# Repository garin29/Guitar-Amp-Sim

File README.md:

# Guitar-Amp-Sim
Guitar Amp Sim

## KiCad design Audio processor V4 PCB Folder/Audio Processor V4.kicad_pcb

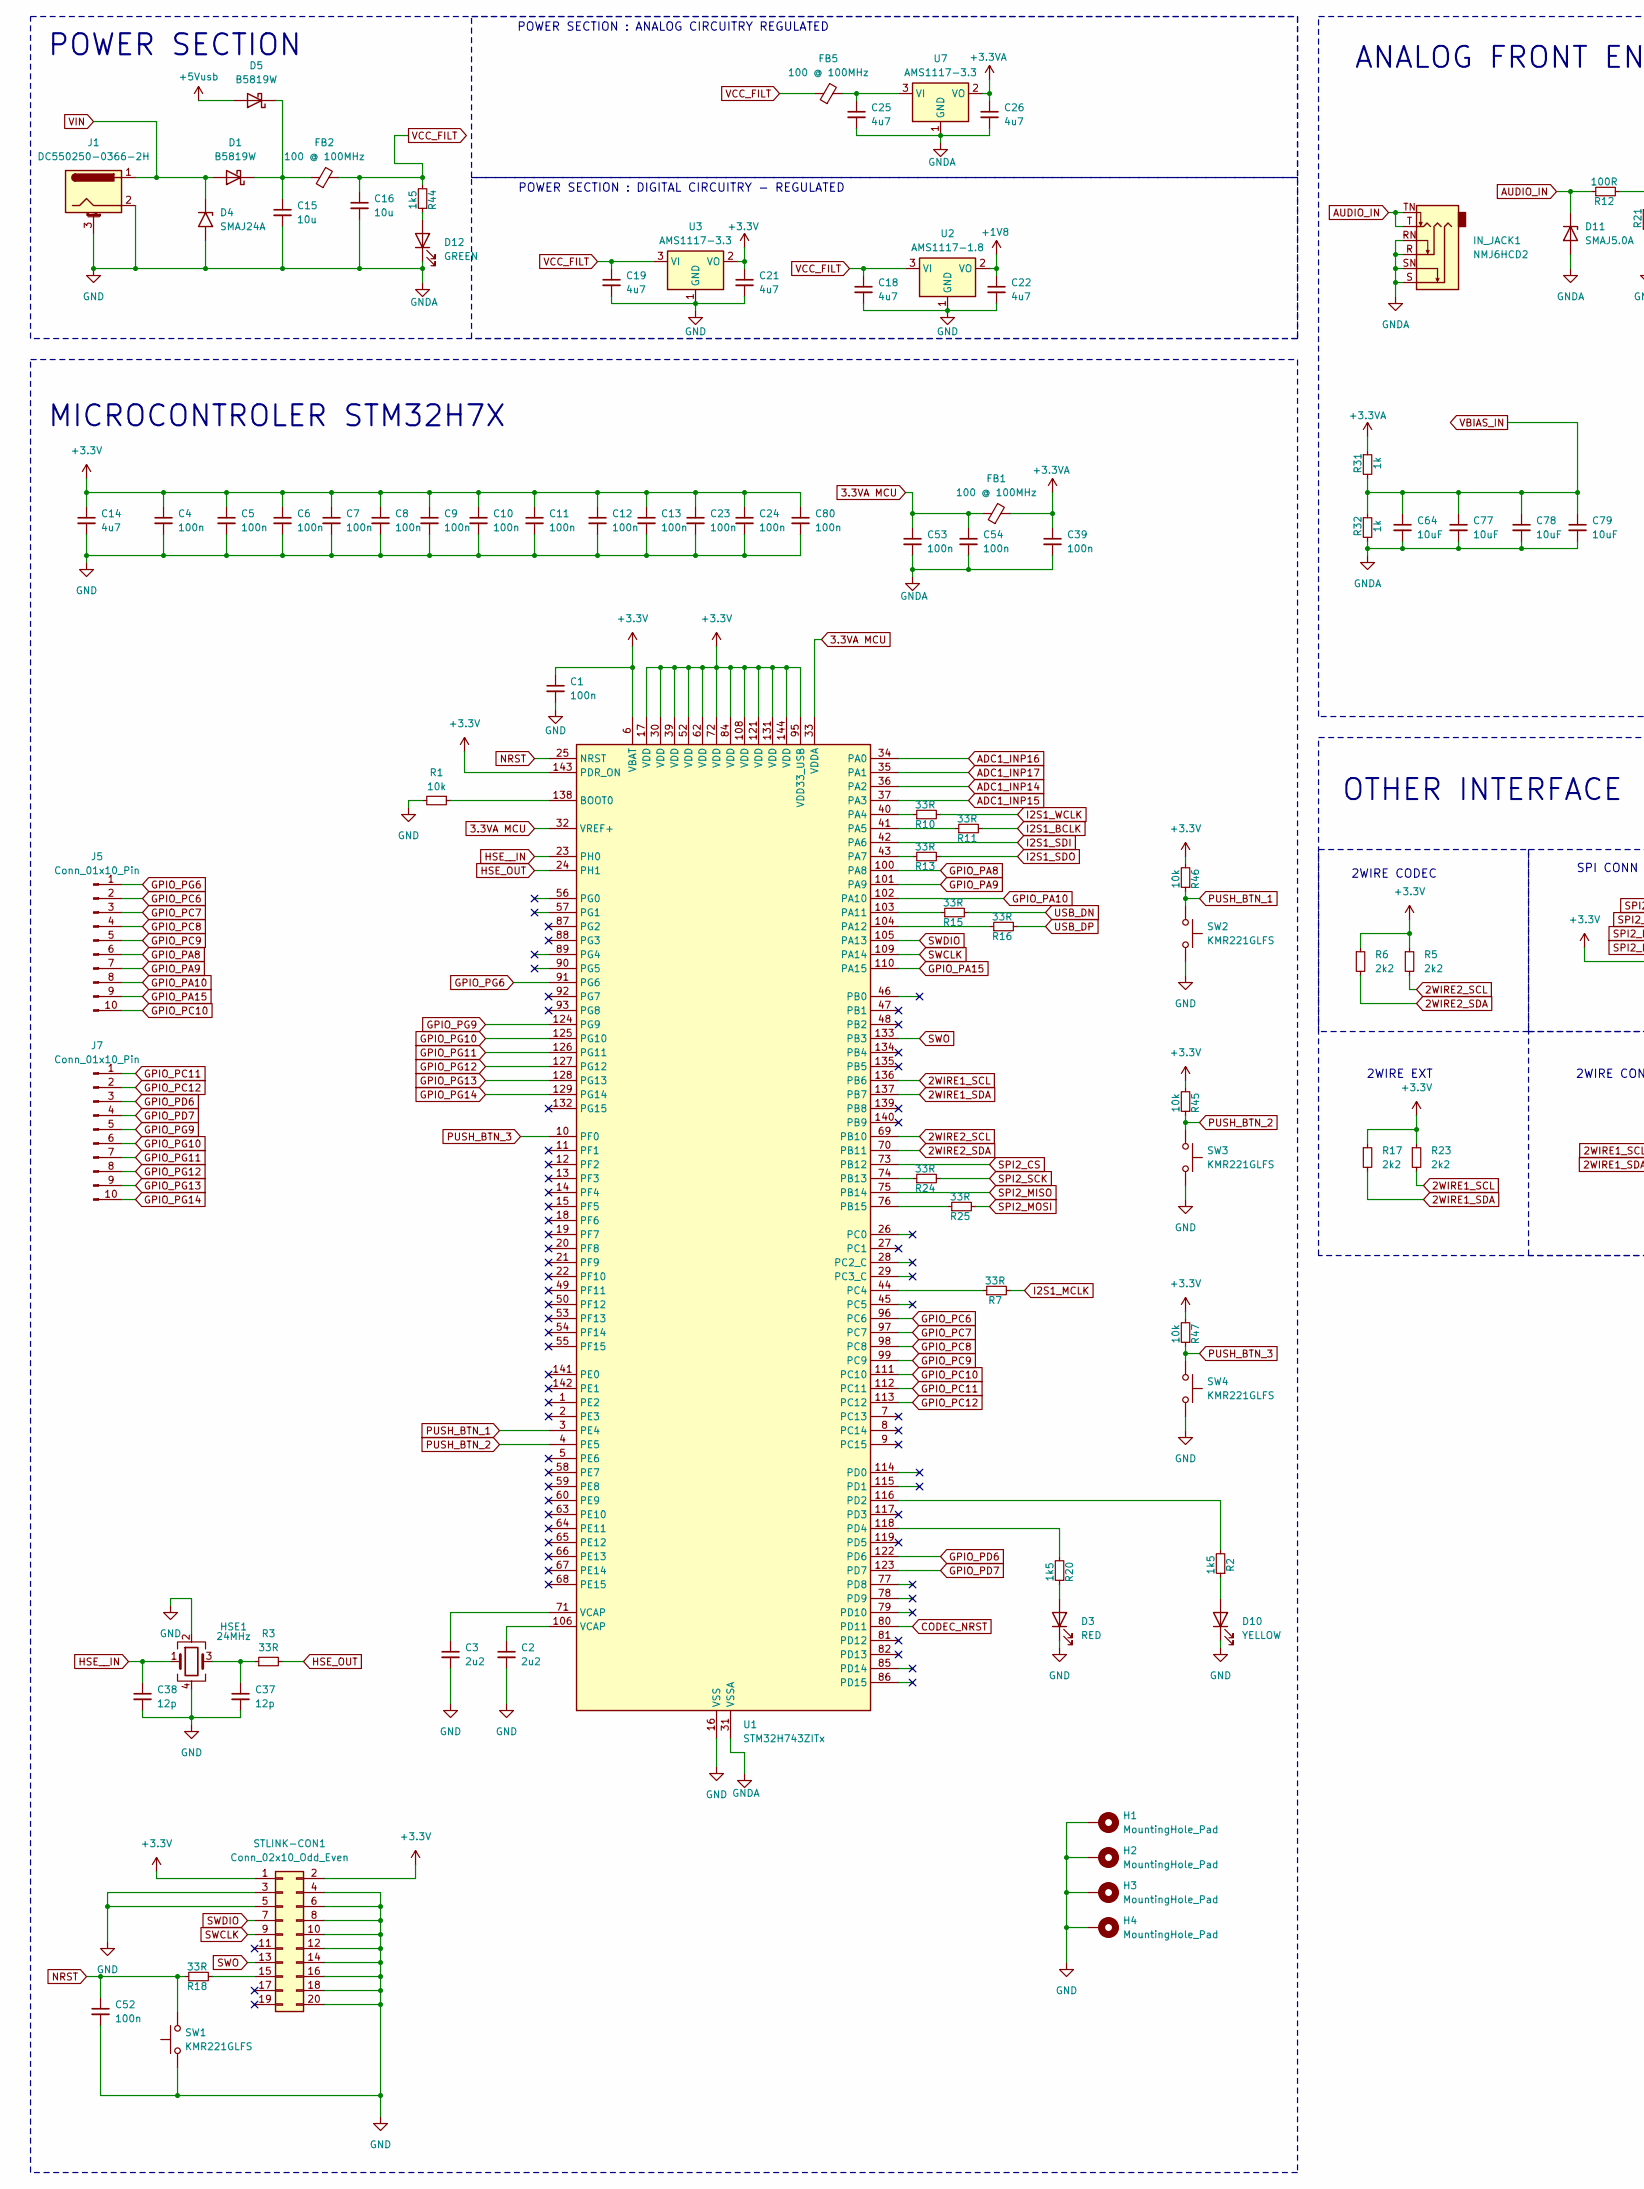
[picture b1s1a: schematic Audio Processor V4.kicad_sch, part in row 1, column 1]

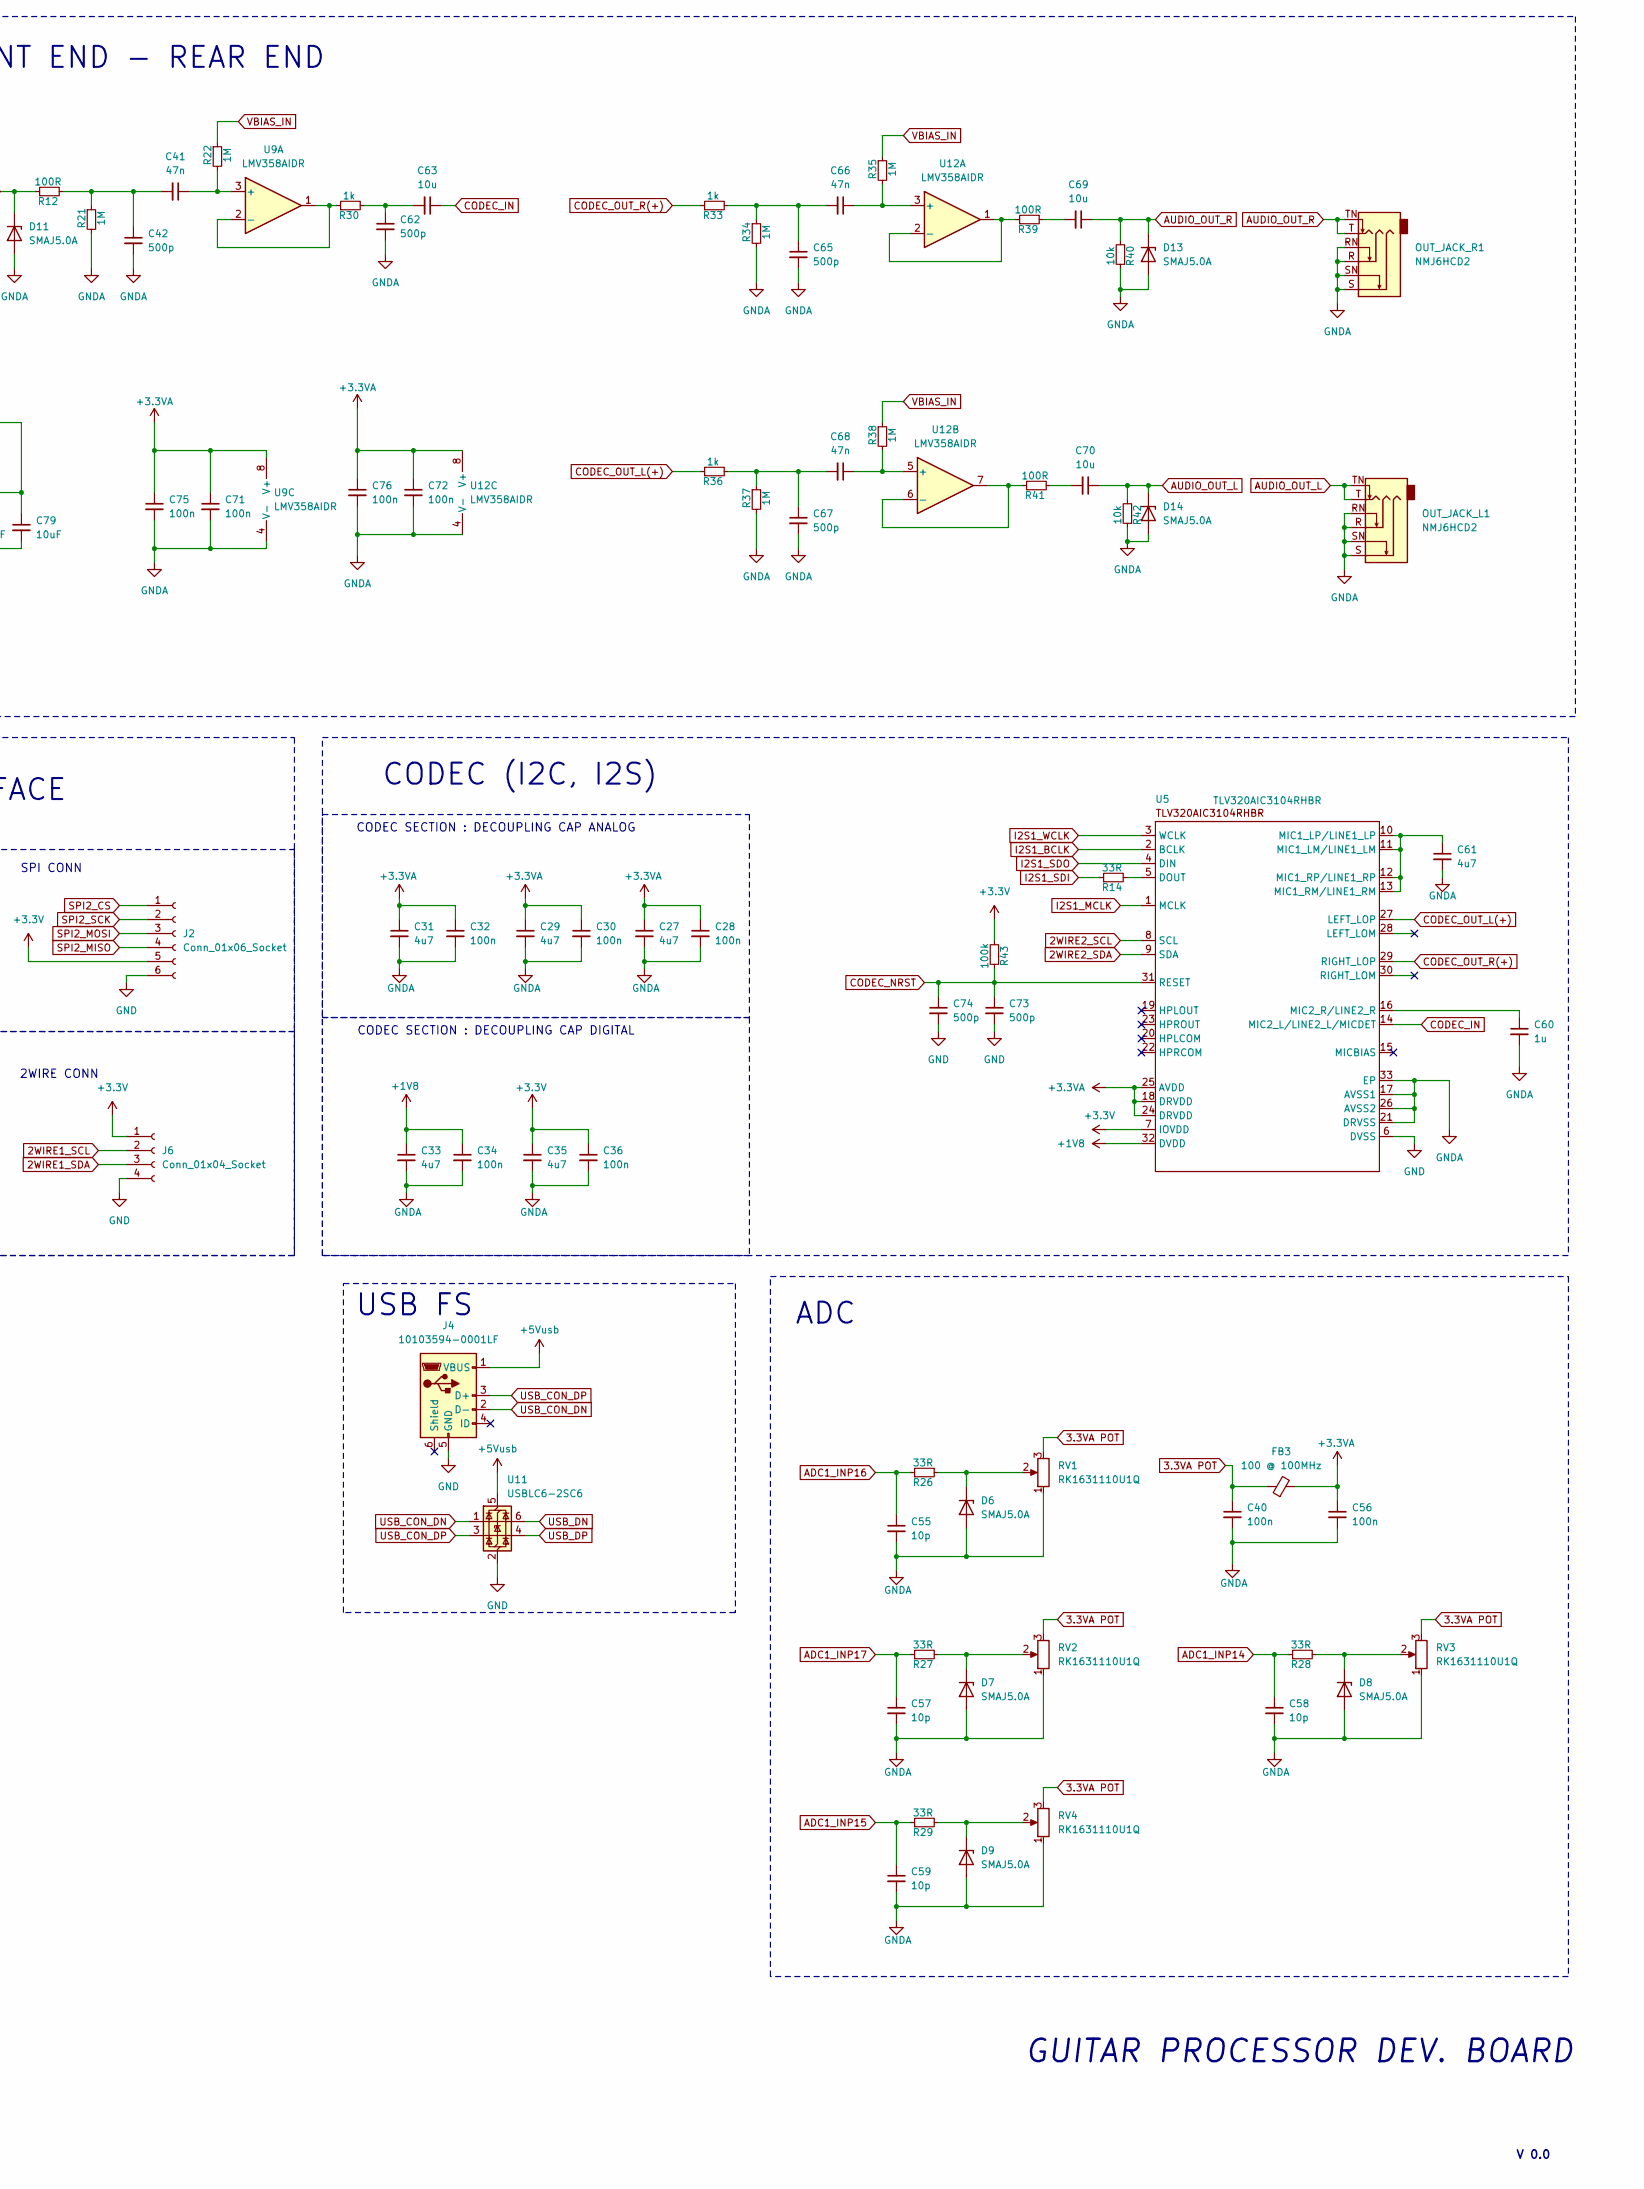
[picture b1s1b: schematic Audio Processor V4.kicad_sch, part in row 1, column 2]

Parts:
C1, C4, C5, C6, C7, C8, C9, C10, C11, C12, C13, C23, C24, C28, C30, C32, C34, C36, C39, C40, C52, C53, C54, C56, C71, C72, C75, C76, C80: 100n; C_0402_1005Metric; LCSC C1525
C2, C3: 2u2; C_0603_1608Metric; LCSC C1607
C14: 4u7; C_0603_1608Metric; LCSC C1705
C15, C16: 10u; C_1206_3216Metric; LCSC C1849
C18, C19, C21, C22, C25, C26, C27, C29, C31, C33, C35, C61: 4u7; C_0805_2012Metric; LCSC C1746
C37, C38: 12p; C_0402_1005Metric; LCSC C1547
C41, C66, C68: 47n; C_0603_1608Metric; LCSC C1622
C42: 500p; C_0603_1608Metric; LCSC C1747
C55, C57, C58, C59: 10p; C_0603_1608Metric; LCSC C1634
C60: 1u; C_0603_1608Metric; LCSC C1592
C62, C65, C67, C73, C74: 500p; C_0805_2012Metric; LCSC C1747
C63, C69, C70: 10u; C_0805_2012Metric; LCSC C1713
C64, C77, C78, C79: 10uF; C_0805_2012Metric; LCSC C1713
D1, D5: B5819W; D_SOD-123; LCSC C64885
D3: RED; LED_0603_1608Metric; LCSC C2286
D4: SMAJ24A; D_SMA; LCSC C148222
D6, D7, D8, D9, D11, D13, D14: SMAJ5.0A; D_SMA; LCSC C113952
D10: YELLOW; LED_0603_1608Metric; LCSC C2287
D12: GREEN; LED_0805_2012Metric; LCSC C2297
FB1, FB2, FB3, FB5: 100 @ 100MHz; L_0805_2012Metric; LCSC C1015
H1, H2, H3, H4: MountingHole_Pad; MountingHole_4.3mm_M4_Pad_Via
HSE1: 24MHz; Crystal_SMD_3225-4Pin_3.2x2.5mm; LCSC C15643
IN_JACK1: NMJ6HCD2; Jack_6.35mm_Neutrik_NMJ6HCD2_Horizontal; LCSC C368502
J1: DC550250-0366-2H; BarrelJack_Horizontal; LCSC C7428747
J2: Conn_01x06_Socket; PinSocket_1x06_P2.54mm_Vertical; LCSC C40877
J4: 10103594-0001LF; USB_Micro-B_Amphenol_10103594-0001LF_Horizontal; LCSC C428495
J5, J7: Conn_01x10_Pin; PinSocket_1x10_P2.54mm_Vertical; LCSC C22438160
J6: Conn_01x04_Socket; PinSocket_1x04_P2.54mm_Vertical; LCSC C2718488
OUT_JACK_L1: NMJ6HCD2; Jack_6.35mm_Neutrik_NMJ6HCD2_Horizontal; LCSC C368502
OUT_JACK_R1: NMJ6HCD2; Jack_6.35mm_Neutrik_NMJ6HCD2_Horizontal; LCSC C368502
R1, R40, R42, R45, R46, R47: 10k; R_0402_1005Metric; LCSC C25744
R2, R20, R44: 1k5; R_0603_1608Metric; LCSC C22843
R3, R7, R10, R11, R13, R14, R15, R16, R18, R24, R25, R26, R27, R28, R29: 33R; R_0402_1005Metric; LCSC C25105
R5, R6, R17, R23: 2k2; R_0603_1608Metric; LCSC C4190
R12, R39, R41: 100R; R_0402_1005Metric; LCSC C25076
R21, R22, R34, R35, R37, R38: 1M; R_0402_1005Metric; LCSC C26083
R30, R31, R32, R33, R36: 1k; R_0402_1005Metric; LCSC C11702
R43: 100k; C_0402_1005Metric; LCSC C25530
RV1, RV2, RV3, RV4: RK1631110U1Q; Potentiometer_Alps_RK163_Single_Horizontal; LCSC C370978
STLINK-CON1: Conn_02x10_Odd_Even; PinHeader_2x10_P2.54mm_Vertical; LCSC C3405
SW1, SW2, SW3, SW4: KMR221GLFS; SW_Push_1P1T_NO_CK_KMR2; LCSC C72443
U1: STM32H743ZITx; LQFP-144_20x20mm_P0.5mm; LCSC C114408
U2: AMS1117-1.8; SOT-223-3_TabPin2; LCSC C6185
U3, U7: AMS1117-3.3; SOT-223-3_TabPin2; LCSC C6186
U5: TLV320AIC3104RHBR; VQFN-32-1EP_5x5mm_P0.5mm_EP3.5x3.5mm_ThermalVias; LCSC C181753
U9, U12: LMV358AIDR; PowerIntegrations_SO-8; LCSC C182039
U11: USBLC6-2SC6; TSOT-23-6; LCSC C2687116

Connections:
2WIRE1_SCL: J6.2, R23.2, U1.136 (PB6)
2WIRE1_SDA: J6.3, R17.2, U1.137 (PB7)
2WIRE2_SCL: R5.2, U1.69 (PB10), U5.8 (SCL)
2WIRE2_SDA: R6.2, U1.70 (PB11), U5.9 (SDA)
3.3VA MCU: C53.1, C54.1, FB1.1, U1.32 (VREF+), U1.33 (VDDA)
3.3VA POT: C40.1, FB3.1, RV1.3, RV2.3, RV3.3, RV4.3
+1V8: C22.1, C33.1, C34.1, U2.2 (VO), U5.32 (DVDD)
+3.3V: C1.1, C4.1, C5.1, C6.1, C7.1, C8.1, C9.1, C10.1, C11.1, C12.1, C13.1, C14.1, C21.1, C23.1, C24.1, C35.1, C36.1, C80.1, J2.5, J6.1, R5.1, R6.1, R17.1, R23.1, R43.2, R45.2, R46.2, R47.2, STLINK-CON1.1, STLINK-CON1.2, U1.6 (VBAT), U1.17 (VDD), U1.30 (VDD), U1.39 (VDD), U1.52 (VDD), U1.62 (VDD), U1.72 (VDD), U1.84 (VDD), U1.95 (VDD33_USB), U1.108 (VDD), U1.121 (VDD), U1.131 (VDD), U1.143 (PDR_ON), U1.144 (VDD), U3.2 (VO), U5.7 (IOVDD)
+3.3VA: C26.1, C27.1, C28.1, C29.1, C30.1, C31.1, C32.1, C39.1, C56.1, C71.1, C72.1, C75.1, C76.1, FB1.2, FB3.2, R31.1, U5.18 (DRVDD), U5.24 (DRVDD), U5.25 (AVDD), U7.2 (VO), U9.8 (V+), U12.8 (V+)
+5Vusb: D5.2 (A), J4.1 (VBUS), U11.5 (VBUS)
ADC1_INP14: C58.1, R28.1, U1.36 (PA2)
ADC1_INP15: C59.1, R29.1, U1.37 (PA3)
ADC1_INP16: C55.1, R26.1, U1.34 (PA0)
ADC1_INP17: C57.1, R27.1, U1.35 (PA1)
AUDIO_IN: D11.1 (K), IN_JACK1.T, IN_JACK1.TN, R12.1
AUDIO_OUT_L: C70.1, D14.1 (K), OUT_JACK_L1.T, OUT_JACK_L1.TN, R42.2
AUDIO_OUT_R: C69.1, D13.1 (K), OUT_JACK_R1.T, OUT_JACK_R1.TN, R40.2
CODEC_IN: C63.1, U5.14 (MIC2_L/LINE2_L/MICDET)
CODEC_NRST: C73.1, C74.1, R43.1, U1.80 (PD11), U5.31 (RESET)
CODEC_OUT_L(+): R36.1, U5.27 (LEFT_LOP)
CODEC_OUT_R(+): R33.1, U5.29 (RIGHT_LOP)
GND: C1.2, C2.2, C3.2, C4.2, C5.2, C6.2, C7.2, C8.2, C9.2, C10.2, C11.2, C12.2, C13.2, C14.2, C15.2, C16.2, C18.2, C19.2, C21.2, C22.2, C23.2, C24.2, C25.2, C26.2, C27.2, C28.2, C29.2, C30.2, C31.2, C32.2, C33.2, C34.2, C35.2, C36.2, C37.2, C38.2, C39.2, C40.2, C42.2, C52.2, C53.2, C54.2, C55.2, C56.2, C57.2, C58.2, C59.2, C60.2, C61.2, C62.2, C64.2, C65.2, C67.2, C71.2, C72.2, C73.2, C74.2, C75.2, C76.2, C77.2, C78.2, C79.2, C80.2, D3.1 (K), D4.2 (A2), D6.2 (A), D7.2 (A), D8.2 (A), D9.2 (A), D10.1 (K), D11.2 (A), D12.1 (K), D13.2 (A), D14.2 (A), H1.1, H2.1, H3.1, H4.1, HSE1.2, HSE1.4, IN_JACK1.R, IN_JACK1.RN, IN_JACK1.S, IN_JACK1.SN, J1.2, J1.3 (MountPin), J2.6, J4.5 (GND), J6.4, OUT_JACK_L1.R, OUT_JACK_L1.RN, OUT_JACK_L1.S, OUT_JACK_L1.SN, OUT_JACK_R1.R, OUT_JACK_R1.RN, OUT_JACK_R1.S, OUT_JACK_R1.SN, R1.2, R21.2, R32.2, R34.2, R37.2, R40.1, R42.1, RV1.1, RV2.1, RV3.1, RV4.1, STLINK-CON1.3, STLINK-CON1.4, STLINK-CON1.5, STLINK-CON1.6, STLINK-CON1.8, STLINK-CON1.10, STLINK-CON1.12, STLINK-CON1.14, STLINK-CON1.16, STLINK-CON1.18, STLINK-CON1.20, SW1.1, SW2.2, SW3.2, SW4.2, U1.16 (VSS), U1.31 (VSSA), U1.38 (VSS), U1.51 (VSS), U1.61 (VSS), U1.83 (VSS), U1.94 (VSS), U1.107 (VSS), U1.120 (VSS), U1.130 (VSS), U2.1 (GND), U3.1 (GND), U5.6 (DVSS), U5.17 (AVSS1), U5.21 (DRVSS), U5.26 (AVSS2), U5.33 (EP), U7.1 (GND), U9.4 (V-), U11.2 (GND), U12.4 (V-)
GPIO_PA8: J5.6, U1.100 (PA8)
GPIO_PA9: J5.7, U1.101 (PA9)
GPIO_PA10: J5.8, U1.102 (PA10)
GPIO_PA15: J5.9, U1.110 (PA15)
GPIO_PC6: J5.2, U1.96 (PC6)
GPIO_PC7: J5.3, U1.97 (PC7)
GPIO_PC8: J5.4, U1.98 (PC8)
GPIO_PC9: J5.5, U1.99 (PC9)
GPIO_PC10: J5.10, U1.111 (PC10)
GPIO_PC11: J7.1, U1.112 (PC11)
GPIO_PC12: J7.2, U1.113 (PC12)
GPIO_PD6: J7.3, U1.122 (PD6)
GPIO_PD7: J7.4, U1.123 (PD7)
GPIO_PG6: J5.1, U1.91 (PG6)
GPIO_PG9: J7.5, U1.124 (PG9)
GPIO_PG10: J7.6, U1.125 (PG10)
GPIO_PG11: J7.7, U1.126 (PG11)
GPIO_PG12: J7.8, U1.127 (PG12)
GPIO_PG13: J7.9, U1.128 (PG13)
GPIO_PG14: J7.10, U1.129 (PG14)
HSE_OUT: R3.2, U1.24 (PH1)
HSE__IN: C38.1, HSE1.1, U1.23 (PH0)
I2S1_BCLK: R11.2, U5.2 (BCLK)
I2S1_MCLK: R7.2, U5.1 (MCLK)
I2S1_SDI: R14.1, U1.42 (PA6)
I2S1_SDO: R13.2, U5.4 (DIN)
I2S1_WCLK: R10.2, U5.3 (WCLK)
NRST: C52.1, R18.1, SW1.2, U1.25 (NRST)
unnamed: C2.1, U1.106 (VCAP)
unnamed: C3.1, U1.71 (VCAP)
unnamed: C37.1, HSE1.3, R3.1
unnamed: C41.2, C42.1, R12.2, R21.1
unnamed: C62.1, C63.2, R30.2
unnamed: C65.1, C66.2, R33.2, R34.1
unnamed: C67.1, C68.2, R36.2, R37.1
unnamed: C69.2, R39.2
unnamed: C70.2, R41.2
unnamed: C15.1, D1.1 (K), D5.1 (K), FB2.1
unnamed: D3.2 (A), R20.1
unnamed: D6.1 (K), R26.2, RV1.2
unnamed: D7.1 (K), R27.2, RV2.2
unnamed: D8.1 (K), R28.2, RV3.2
unnamed: D9.1 (K), R29.2, RV4.2
unnamed: D10.2 (A), R2.1
unnamed: D12.2 (A), R44.1
unnamed: R18.2, STLINK-CON1.15
unnamed: R1.1, U1.138 (BOOT0)
unnamed: R10.1, U1.40 (PA4)
unnamed: R11.1, U1.41 (PA5)
unnamed: R13.1, U1.43 (PA7)
unnamed: R15.1, U1.103 (PA11)
unnamed: R16.1, U1.104 (PA12)
unnamed: R24.1, U1.74 (PB13)
unnamed: R25.1, U1.76 (PB15)
unnamed: R7.1, U1.44 (PC4)
unnamed: R2.2, U1.116 (PD2)
unnamed: R20.2, U1.118 (PD4)
unnamed: R14.2, U5.5 (DOUT)
unnamed: C61.1, U5.10 (MIC1_LP/LINE1_LP), U5.11 (MIC1_LM/LINE1_LM), U5.12 (MIC1_RP/LINE1_RP), U5.13 (MIC1_RM/LINE1_RM)
unnamed: C60.1, U5.16 (MIC2_R/LINE2_R)
unnamed: C25.1, FB5.2, U7.3 (VI)
unnamed: C41.1, R22.2, U9.3 (+)
unnamed: R30.1, U9.1, U9.2 (-)
unnamed: C66.1, R35.2, U12.3 (+)
unnamed: R39.1, U12.1, U12.2 (-)
unnamed: C68.1, R38.2, U12.5 (+)
unnamed: R41.1, U12.6 (-), U12.7
PUSH_BTN_1: R46.1, SW2.1, U1.3 (PE4)
PUSH_BTN_2: R45.1, SW3.1, U1.4 (PE5)
PUSH_BTN_3: R47.1, SW4.1, U1.10 (PF0)
SPI2_CS: J2.1, U1.73 (PB12)
SPI2_MISO: J2.4, U1.75 (PB14)
SPI2_MOSI: J2.3, R25.2
SPI2_SCK: J2.2, R24.2
SWCLK: STLINK-CON1.9, U1.109 (PA14)
SWDIO: STLINK-CON1.7, U1.105 (PA13)
SWO: STLINK-CON1.13, U1.133 (PB3)
USB_CON_DN: J4.2 (D-), U11.1 (I/O1)
USB_CON_DP: J4.3 (D+), U11.3 (I/O2)
USB_DN: R15.2, U11.6 (I/O1)
USB_DP: R16.2, U11.4 (I/O2)
VBIAS_IN: C64.1, C77.1, C78.1, C79.1, R22.1, R31.2, R32.1, R35.1, R38.1
VCC_FILT: C16.1, C18.1, C19.1, FB2.2, FB5.1, R44.2, U2.3 (VI), U3.3 (VI)
VIN: D1.2 (A), D4.1 (A1), J1.1

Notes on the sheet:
MICROCONTROLER STM32H7X
OTHER INTERFACE
POWER SECTION : DIGITAL CIRCUITRY - REGULATED
CODEC SECTION : DECOUPLING CAP DIGITAL
POWER SECTION : ANALOG CIRCUITRY REGULATED
GUITAR PROCESSOR DEV. BOARD
2WIRE CODEC
USB FS
POWER SECTION
SPI CONN
CODEC SECTION : DECOUPLING CAP ANALOG
ANALOG FRONT END - REAR END
CODEC (I2C, I2S)
V 0.0
2WIRE EXT
ADC
2WIRE CONN

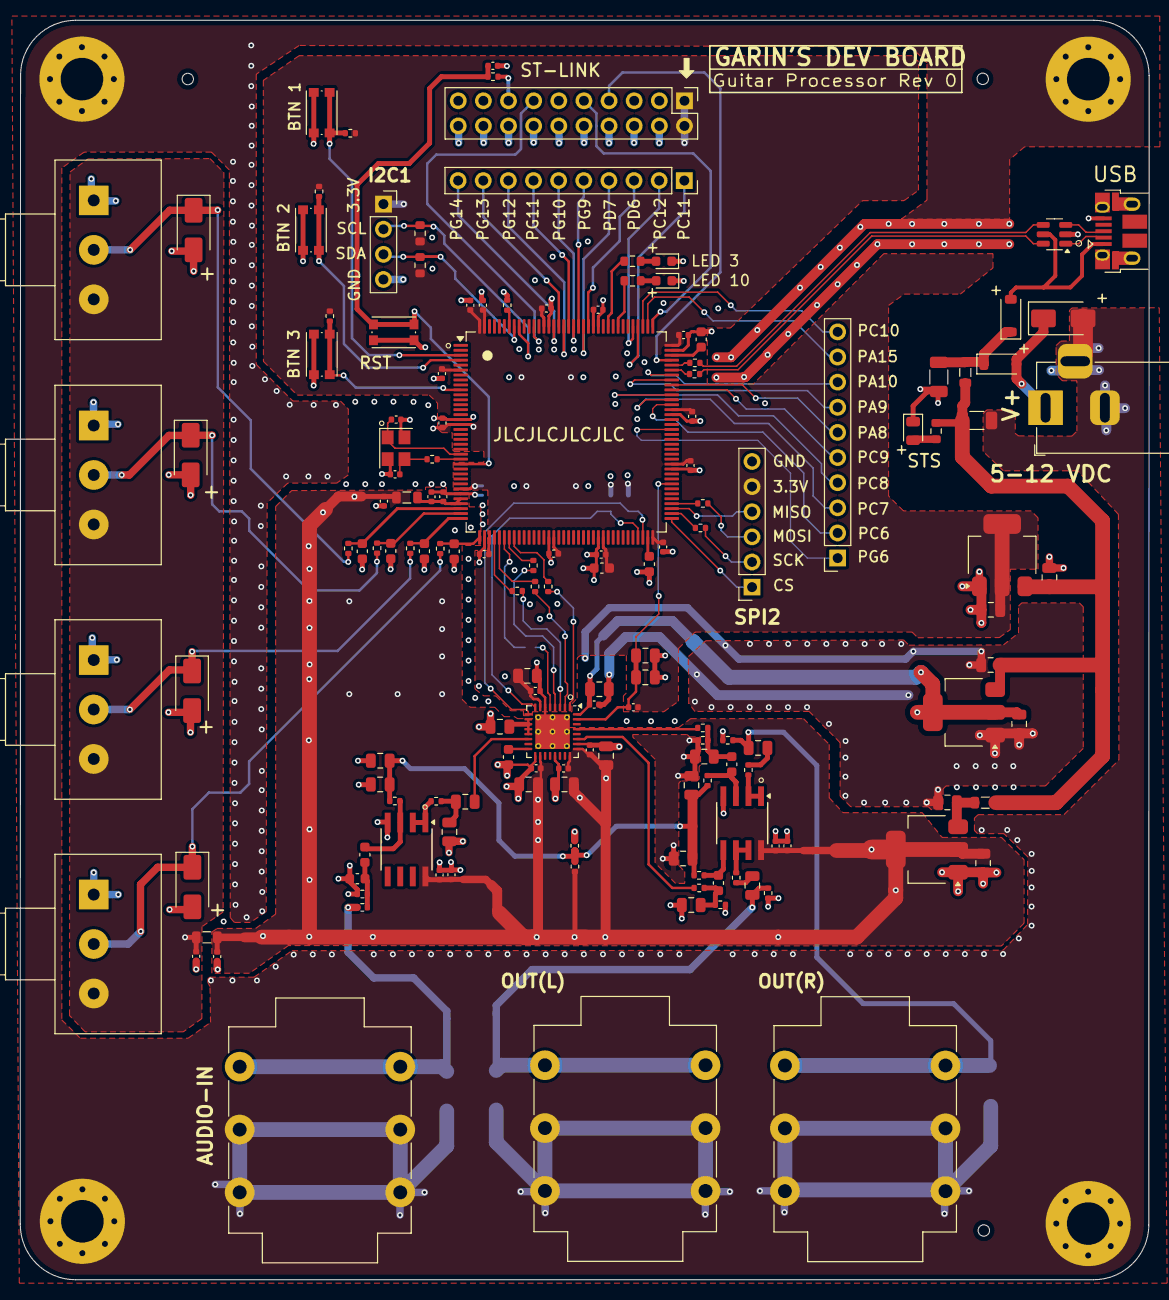
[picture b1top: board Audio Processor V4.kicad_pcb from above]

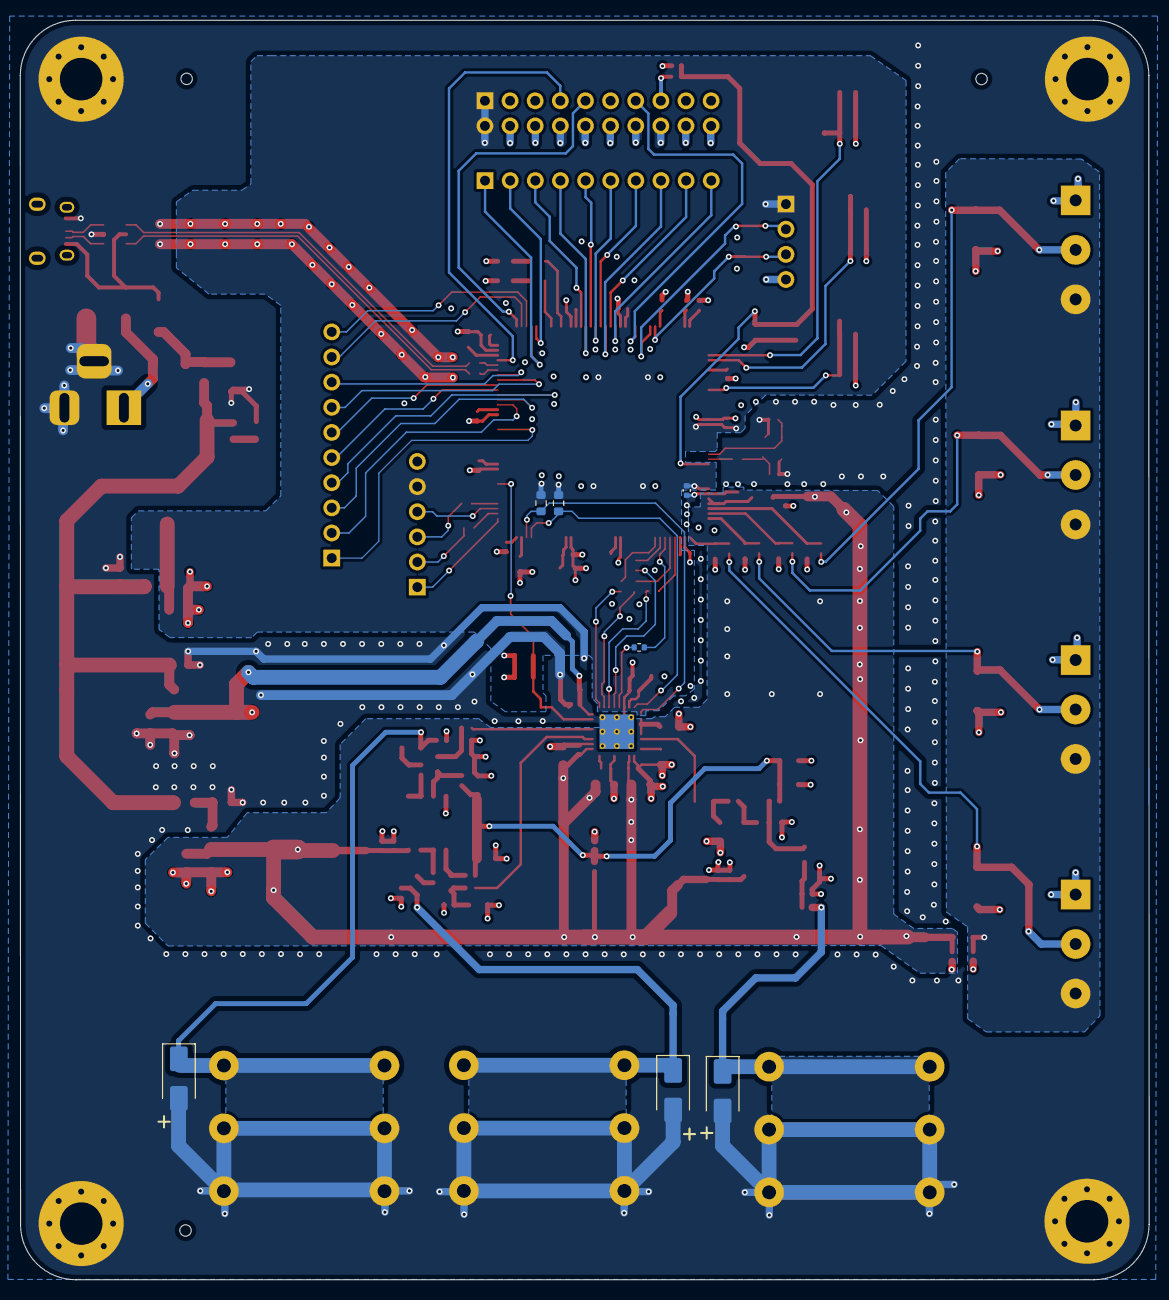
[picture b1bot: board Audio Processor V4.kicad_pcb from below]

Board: 4 copper layers, 114.1 x 127.3 mm, 160 parts (7 on the bottom side), 106 nets.

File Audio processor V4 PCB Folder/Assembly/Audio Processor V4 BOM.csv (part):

"Comment","Designator","Footprint","LCSC"
"Conn_01x10_Pin","J7","Connector_PinSocket_2.54mm:PinSocket_1x10_P2.54mm_Vertical","C22438160"
"Conn_01x10_Pin","J5","Connector_PinSocket_2.54mm:PinSocket_1x10_P2.54mm_Vertical","C22438160"
"DC550250-0366-2H","J1","Connector_BarrelJack:BarrelJack_Horizontal","C7428747"
"Conn_01x04_Socket","J6","Connector_PinSocket_2.54mm:PinSocket_1x04_P2.54mm_Vertical","C2718488"
"USBLC6-2SC6","U11","Package_TO_SOT_SMD:TSOT-23-6","C2687116"
"10103594-0001LF","J4","Connector_USB:USB_Micro-B_Amphenol_10103594-0001LF_Horizontal","C428495"
"RK1631110U1Q","RV4","Potentiometer_THT:Potentiometer_Alps_RK163_Single_Horizontal","C370978"
"RK1631110U1Q","RV3","Potentiometer_THT:Potentiometer_Alps_RK163_Single_Horizontal","C370978"
"RK1631110U1Q","RV2","Potentiometer_THT:Potentiometer_Alps_RK163_Single_Horizontal","C370978"
"RK1631110U1Q","RV1","Potentiometer_THT:Potentiometer_Alps_RK163_Single_Horizontal","C370978"
"NMJ6HCD2","OUT_JACK_R1","Connector_Audio:Jack_6.35mm_Neutrik_NMJ6HCD2_Horizontal","C368502"
"NMJ6HCD2","OUT_JACK_L1","Connector_Audio:Jack_6.35mm_Neutrik_NMJ6HCD2_Horizontal","C368502"
"NMJ6HCD2","IN_JACK1","Connector_Audio:Jack_6.35mm_Neutrik_NMJ6HCD2_Horizontal","C368502"
"LMV358AIDR","U12","Package_SO:PowerIntegrations_SO-8","C182039"
"LMV358AIDR","U9","Package_SO:PowerIntegrations_SO-8","C182039"
"TLV320AIC3104RHBR","U5","Package_DFN_QFN:VQFN-32-1EP_5x5mm_P0.5mm_EP3.5x3.5mm_ThermalVias","C181753"
"SMAJ24A","D4","Diode_SMD:D_SMA","C148222"
"STM32H743ZITx","U1","Package_QFP:LQFP-144_20x20mm_P0.5mm","C114408"
"SMAJ5.0A","D14","Diode_SMD:D_SMA","C113952"
"SMAJ5.0A","D13","Diode_SMD:D_SMA","C113952"
"SMAJ5.0A","D11","Diode_SMD:D_SMA","C113952"
"SMAJ5.0A","D9","Diode_SMD:D_SMA","C113952"
"SMAJ5.0A","D8","Diode_SMD:D_SMA","C113952"
"SMAJ5.0A","D7","Diode_SMD:D_SMA","C113952"
"SMAJ5.0A","D6","Diode_SMD:D_SMA","C113952"
"KMR221GLFS","SW4","Button_Switch_SMD:SW_Push_1P1T_NO_CK_KMR2","C72443"
"KMR221GLFS","SW3","Button_Switch_SMD:SW_Push_1P1T_NO_CK_KMR2","C72443"
"KMR221GLFS","SW2","Button_Switch_SMD:SW_Push_1P1T_NO_CK_KMR2","C72443"
"KMR221GLFS","SW1","Button_Switch_SMD:SW_Push_1P1T_NO_CK_KMR2","C72443"
"B5819W","D5","Diode_SMD:D_SOD-123","C64885"
"B5819W","D1","Diode_SMD:D_SOD-123","C64885"
"Conn_01x06_Socket","J2","Connector_PinSocket_2.54mm:PinSocket_1x06_P2.54mm_Vertical","C40877"
"1M","R38","Resistor_SMD:R_0402_1005Metric","C26083"
"1M","R37","Resistor_SMD:R_0402_1005Metric","C26083"
"1M","R35","Resistor_SMD:R_0402_1005Metric","C26083"
"1M","R34","Resistor_SMD:R_0402_1005Metric","C26083"
"1M","R22","Resistor_SMD:R_0402_1005Metric","C26083"
"1M","R21","Resistor_SMD:R_0402_1005Metric","C26083"
"10k","R47","Resistor_SMD:R_0402_1005Metric","C25744"
"10k","R46","Resistor_SMD:R_0402_1005Metric","C25744"
"10k","R45","Resistor_SMD:R_0402_1005Metric","C25744"
"10k","R42","Resistor_SMD:R_0402_1005Metric","C25744"
"10k","R40","Resistor_SMD:R_0402_1005Metric","C25744"
"10k","R1","Resistor_SMD:R_0402_1005Metric","C25744"
"100k","R43","Capacitor_SMD:C_0402_1005Metric","C25530"
"33R","R29","Resistor_SMD:R_0402_1005Metric","C25105"
"33R","R28","Resistor_SMD:R_0402_1005Metric","C25105"
"33R","R27","Resistor_SMD:R_0402_1005Metric","C25105"
"33R","R26","Resistor_SMD:R_0402_1005Metric","C25105"
"33R","R25","Resistor_SMD:R_0402_1005Metric","C25105"
"33R","R24","Resistor_SMD:R_0402_1005Metric","C25105"
"33R","R18","Resistor_SMD:R_0402_1005Metric","C25105"
"33R","R16","Resistor_SMD:R_0402_1005Metric","C25105"
"33R","R15","Resistor_SMD:R_0402_1005Metric","C25105"
"33R","R14","Resistor_SMD:R_0402_1005Metric","C25105"
"33R","R13","Resistor_SMD:R_0402_1005Metric","C25105"
"33R","R11","Resistor_SMD:R_0402_1005Metric","C25105"
"33R","R10","Resistor_SMD:R_0402_1005Metric","C25105"
"33R","R7","Resistor_SMD:R_0402_1005Metric","C25105"
"33R","R3","Resistor_SMD:R_0402_1005Metric","C25105"
"100R","R41","Resistor_SMD:R_0402_1005Metric","C25076"
"100R","R39","Resistor_SMD:R_0402_1005Metric","C25076"
"100R","R12","Resistor_SMD:R_0402_1005Metric","C25076"
"1k5","R44","Resistor_SMD:R_0603_1608Metric","C22843"
"1k5","R20","Resistor_SMD:R_0603_1608Metric","C22843"
"1k5","R2","Resistor_SMD:R_0603_1608Metric","C22843"
"24MHz","HSE1","Crystal:Crystal_SMD_3225-4Pin_3.2x2.5mm","C15643"
"1k","R36","Resistor_SMD:R_0402_1005Metric","C11702"
"1k","R33","Resistor_SMD:R_0402_1005Metric","C11702"
"1k","R32","Resistor_SMD:R_0402_1005Metric","C11702"
"1k","R31","Resistor_SMD:R_0402_1005Metric","C11702"
"1k","R30","Resistor_SMD:R_0402_1005Metric","C11702"
"AMS1117-3.3","U7","Package_TO_SOT_SMD:SOT-223-3_TabPin2","C6186"
"AMS1117-3.3","U3","Package_TO_SOT_SMD:SOT-223-3_TabPin2","C6186"
"AMS1117-1.8","U2","Package_TO_SOT_SMD:SOT-223-3_TabPin2","C6185"
"2k2","R23","Resistor_SMD:R_0603_1608Metric","C4190"
"2k2","R17","Resistor_SMD:R_0603_1608Metric","C4190"
"2k2","R6","Resistor_SMD:R_0603_1608Metric","C4190"
"2k2","R5","Resistor_SMD:R_0603_1608Metric","C4190"
"Conn_02x10_Odd_Even","STLINK-CON1","Connector_PinHeader_2.54mm:PinHeader_2x10_P2.54mm_Vertical","C3405"
"GREEN","D12","LED_SMD:LED_0805_2012Metric","C2297"
"YELLOW","D10","LED_SMD:LED_0603_1608Metric","C2287"
"RED","D3","LED_SMD:LED_0603_1608Metric","C2286"
"10u","C16","Capacitor_SMD:C_1206_3216Metric","C1849"
"10u","C15","Capacitor_SMD:C_1206_3216Metric","C1849"
"500p","C74","Capacitor_SMD:C_0805_2012Metric","C1747"
"500p","C73","Capacitor_SMD:C_0805_2012Metric","C1747"
"500p","C67","Capacitor_SMD:C_0805_2012Metric","C1747"
"500p","C65","Capacitor_SMD:C_0805_2012Metric","C1747"
"500p","C62","Capacitor_SMD:C_0805_2012Metric","C1747"
"500p","C42","Capacitor_SMD:C_0603_1608Metric","C1747"
"4u7","C61","Capacitor_SMD:C_0805_2012Metric","C1746"
"4u7","C35","Capacitor_SMD:C_0805_2012Metric","C1746"
"4u7","C33","Capacitor_SMD:C_0805_2012Metric","C1746"
"4u7","C31","Capacitor_SMD:C_0805_2012Metric","C1746"
"4u7","C29","Capacitor_SMD:C_0805_2012Metric","C1746"
"4u7","C27","Capacitor_SMD:C_0805_2012Metric","C1746"
"4u7","C26","Capacitor_SMD:C_0805_2012Metric","C1746"
"4u7","C25","Capacitor_SMD:C_0805_2012Metric","C1746"
"4u7","C22","Capacitor_SMD:C_0805_2012Metric","C1746"
"4u7","C21","Capacitor_SMD:C_0805_2012Metric","C1746"
"4u7","C19","Capacitor_SMD:C_0805_2012Metric","C1746"
"4u7","C18","Capacitor_SMD:C_0805_2012Metric","C1746"
"10uF","C79","Capacitor_SMD:C_0805_2012Metric","C1713"
"10uF","C78","Capacitor_SMD:C_0805_2012Metric","C1713"
"10uF","C77","Capacitor_SMD:C_0805_2012Metric","C1713"
"10u","C70","Capacitor_SMD:C_0805_2012Metric","C1713"
"10u","C69","Capacitor_SMD:C_0805_2012Metric","C1713"
"10uF","C64","Capacitor_SMD:C_0805_2012Metric","C1713"
"10u","C63","Capacitor_SMD:C_0805_2012Metric","C1713"
"4u7","C14","Capacitor_SMD:C_0603_1608Metric","C1705"
"10p","C59","Capacitor_SMD:C_0603_1608Metric","C1634"
"10p","C58","Capacitor_SMD:C_0603_1608Metric","C1634"
"10p","C57","Capacitor_SMD:C_0603_1608Metric","C1634"
"10p","C55","Capacitor_SMD:C_0603_1608Metric","C1634"
"47n","C68","Capacitor_SMD:C_0603_1608Metric","C1622"
"47n","C66","Capacitor_SMD:C_0603_1608Metric","C1622"
"47n","C41","Capacitor_SMD:C_0603_1608Metric","C1622"
"2u2","C3","Capacitor_SMD:C_0603_1608Metric","C1607"
"2u2","C2","Capacitor_SMD:C_0603_1608Metric","C1607"
"1u","C60","Capacitor_SMD:C_0603_1608Metric","C1592"
"12p","C38","Capacitor_SMD:C_0402_1005Metric","C1547"
"12p","C37","Capacitor_SMD:C_0402_1005Metric","C1547"
"100n","C80","Capacitor_SMD:C_0402_1005Metric","C1525"
"100n","C76","Capacitor_SMD:C_0402_1005Metric","C1525"
"100n","C75","Capacitor_SMD:C_0402_1005Metric","C1525"
"100n","C72","Capacitor_SMD:C_0402_1005Metric","C1525"
"100n","C71","Capacitor_SMD:C_0402_1005Metric","C1525"
"100n","C56","Capacitor_SMD:C_0402_1005Metric","C1525"
"100n","C54","Capacitor_SMD:C_0402_1005Metric","C1525"
"100n","C53","Capacitor_SMD:C_0402_1005Metric","C1525"
"100n","C52","Capacitor_SMD:C_0402_1005Metric","C1525"
"100n","C40","Capacitor_SMD:C_0402_1005Metric","C1525"
"100n","C39","Capacitor_SMD:C_0402_1005Metric","C1525"
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
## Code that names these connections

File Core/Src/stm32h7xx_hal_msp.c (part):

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
    __HAL_RCC_GPIOA_CLK_ENABLE();
    /**ADC1 GPIO Configuration
    PA0     ------> ADC1_INP16
    PA1     ------> ADC1_INP17
    PA2     ------> ADC1_INP14
    PA3     ------> ADC1_INP15
    */
    GPIO_InitStruct.Pin = GPIO_PIN_0|GPIO_PIN_1|GPIO_PIN_2|GPIO_PIN_3;
    GPIO_InitStruct.Mode = GPIO_MODE_ANALOG;
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    __HAL_RCC_ADC12_CLK_DISABLE();

    /**ADC1 GPIO Configuration
    PA0     ------> ADC1_INP16
    PA1     ------> ADC1_INP17
    PA2     ------> ADC1_INP14
    PA3     ------> ADC1_INP15
    */
    HAL_GPIO_DeInit(GPIOA, GPIO_PIN_0|GPIO_PIN_1|GPIO_PIN_2|GPIO_PIN_3);

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
    __HAL_RCC_GPIOB_CLK_ENABLE();
    /**I2C1 GPIO Configuration
    PB6     ------> I2C1_SCL
    PB7     ------> I2C1_SDA
    */
    GPIO_InitStruct.Pin = GPIO_PIN_6|GPIO_PIN_7;
    GPIO_InitStruct.Mode = GPIO_MODE_AF_OD;
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
    __HAL_RCC_GPIOB_CLK_ENABLE();
    /**I2C2 GPIO Configuration
    PB10     ------> I2C2_SCL
    PB11     ------> I2C2_SDA
    */
    GPIO_InitStruct.Pin = GPIO_PIN_10|GPIO_PIN_11;
    GPIO_InitStruct.Mode = GPIO_MODE_AF_OD;
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    __HAL_RCC_I2C1_CLK_DISABLE();

    /**I2C1 GPIO Configuration
    PB6     ------> I2C1_SCL
    PB7     ------> I2C1_SDA
    */
    HAL_GPIO_DeInit(GPIOB, GPIO_PIN_6);

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    __HAL_RCC_I2C2_CLK_DISABLE();

    /**I2C2 GPIO Configuration
    PB10     ------> I2C2_SCL
    PB11     ------> I2C2_SDA
    */
    HAL_GPIO_DeInit(GPIOB, GPIO_PIN_10);

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    __HAL_RCC_GPIOA_CLK_ENABLE();
    __HAL_RCC_GPIOC_CLK_ENABLE();
    /**I2S1 GPIO Configuration
    PA4     ------> I2S1_WS
    PA5     ------> I2S1_CK
    PA6     ------> I2S1_SDI
    PA7     ------> I2S1_SDO
    PC4     ------> I2S1_MCK
    */
    GPIO_InitStruct.Pin = GPIO_PIN_4|GPIO_PIN_5|GPIO_PIN_6|GPIO_PIN_7;
    GPIO_InitStruct.Mode = GPIO_MODE_AF_PP;
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    __HAL_RCC_SPI1_CLK_DISABLE();

    /**I2S1 GPIO Configuration
    PA4     ------> I2S1_WS
    PA5     ------> I2S1_CK
    PA6     ------> I2S1_SDI
    PA7     ------> I2S1_SDO
    PC4     ------> I2S1_MCK
    */
    HAL_GPIO_DeInit(GPIOA, GPIO_PIN_4|GPIO_PIN_5|GPIO_PIN_6|GPIO_PIN_7);

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
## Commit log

2025-03-14 Update main.c
    Change post gain LPF to 12k

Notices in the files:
Core/Src/stm32h7xx_hal_msp.c:
Copyright (c) 2024 STMicroelectronics.
All rights reserved.
This software is licensed under terms that can be found in the LICENSE file
